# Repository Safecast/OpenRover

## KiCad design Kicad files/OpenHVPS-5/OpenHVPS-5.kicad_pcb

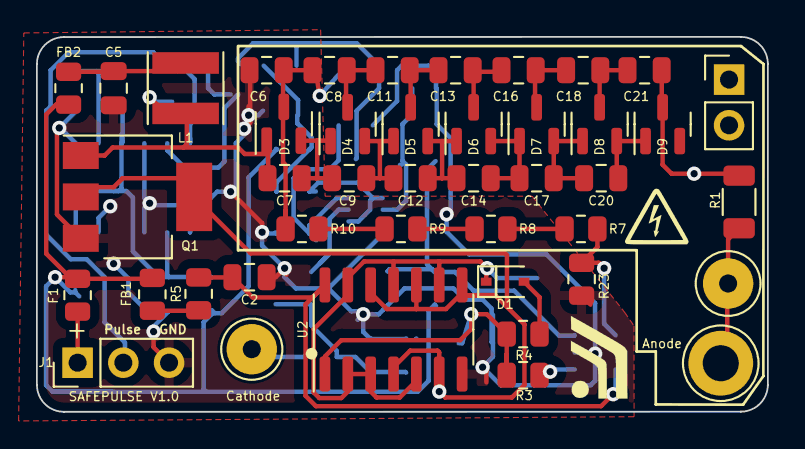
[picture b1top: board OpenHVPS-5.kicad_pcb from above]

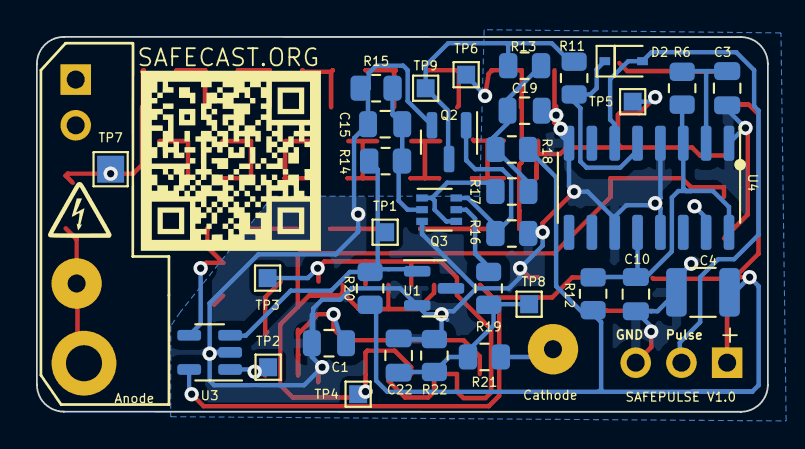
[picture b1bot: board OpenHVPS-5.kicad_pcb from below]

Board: 2 copper layers, 40.6 x 20.8 mm, 77 parts (35 on the bottom side), 43 nets.

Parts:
C1: 150pF; C_0805_2012Metric
C2, C5, C10: 1uF; C_0805_2012Metric
C3, C15: 1nF; C_0805_2012Metric
C4: 10uF; C_1210_3225Metric
C6, C7, C8, C9, C11, C12, C13, C14, C16, C17, C18, C19, C20, C21: 0.1uF; C_0805_2012Metric
C22: 360pF; C_0805_2012Metric
D1, D2: BAS16J; D_SOD-323
D3, D4, D5, D6, D7, D8, D9: BAV23; SOT-23
F1: Polyfuse; R_0805_2012Metric
FB1, FB2: BKP2125HS221-T; R_0805_2012Metric
H1: Cathode; TestPoint_Loop_D2.60mm_Drill1.4mm_Beaded
H2: Anode; TestPoint_Loop_D3.50mm_Drill1.4mm_Beaded
H2#2: Anode; TestPoint_Loop_D3.80mm_Drill2.0mm
J1: Conn_01x03_Male; PinHeader_1x03_P2.54mm_Vertical
L1: 2.2uH; L_Taiyo-Yuden_MD-4040
Q1: FQT7N10; SOT-223-3_TabPin2
Q2: BC846A; SOT-23
Q3: MMDT3906; SOT-363_SC-70-6
R1: 10M; R_1206_3216Metric
R3, R4: 100K; R_0805_2012Metric
R5, R12: 100; R_0805_2012Metric
R6: 121k; R_0805_2012Metric
R7, R8, R9, R10: 22M; R_0805_2012Metric
R11: 33k; R_0805_2012Metric
R13, R19: 100k; R_0805_2012Metric
R14: 1M5; R_0805_2012Metric
R15: 392k; R_0805_2012Metric
R16: 1M; R_0805_2012Metric
R17: 499k; R_0805_2012Metric
R18: 1k; R_0805_2012Metric
R20: 560K; R_0805_2012Metric
R21: 47k; R_0805_2012Metric
R22: 20k; R_0805_2012Metric
R23: 3.16M; R_0805_2012Metric
TP1, TP2, TP3, TP4, TP5, TP6, TP8, TP9: TestPoint; TestPoint_Pad_1.0x1.0mm
TP7: TestPoint; TestPoint_Pad_1.5x1.5mm
U1: MAX6008AEUR+T; SOT-23
U2: 74HC14; SOIC-14_3.9x8.7mm_P1.27mm
U3: MAX4162; SOT-23-5
U4: CD14538BM; SOIC-16_3.9x9.9mm_P1.27mm

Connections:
+2V5: R14.1, R20.2, TP1.1, U1.1 (IN), U3.3 (+)
+3V3: C4.1, F1.2, FB1.1, FB2.1, R12.1, R18.2, R20.1
GND: C1.2, C2.2, C3.2, C4.2, C5.2, C6.1, C10.2, C15.2, C19.2, C22.2, J1.3, Q1.3 (S), Q2.2 (E), Q3.3 (C2), R15.2, R16.2, R22.2, R23.2, U1.2 (OUT), U2.7 (GND), U3.2 (V-), U4.1 (VSS), U4.4 (Clk+), U4.8 (VSS), U4.11 (Clk-), U4.13 (R), U4.15 (VSS)
unnamed: C1.1, R3.1, R4.1, U2.1
unnamed: C2.1, R5.1, U2.14 (VCC), U3.5 (V+)
unnamed: C3.1, R6.2, U4.2 (RxCx)
unnamed: C5.1, FB2.2, L1.1
unnamed: C6.2, C8.1, D3.3 (K), R10.1, TP6.1
unnamed: C7.1, D3.1 (K), L1.2, Q1.1 (D), TP5.1
unnamed: C7.2, C9.1, D3.2 (A), D4.1 (K)
unnamed: C10.1, R6.1, R12.2, U4.3 (R), U4.12 (Clk+), U4.16 (VDD)
unnamed: C8.2, C11.1, D4.3 (K)
unnamed: C11.2, C13.1, D5.3 (K)
unnamed: C9.2, C12.1, D4.2 (A), D5.1 (K)
unnamed: C12.2, C14.1, D5.2 (A), D6.1 (K)
unnamed: C13.2, C16.1, D6.3 (K)
unnamed: C14.2, C17.1, D6.2 (A), D7.1 (K)
unnamed: C15.1, Q3.2 (B1), R14.2, R15.1
unnamed: C16.2, C18.1, D7.3 (K)
unnamed: C17.2, C20.1, D7.2 (A), D8.1 (K)
unnamed: C18.2, C21.1, D8.3 (K)
unnamed: C19.1, R13.1, R17.1, R18.1
unnamed: C20.2, D8.2 (A), D9.1 (K)
unnamed: C21.2, D9.3 (K), R1.1, TP7.1
unnamed: C22.1, R19.2, R21.2, R22.1, TP8.1
unnamed: D1.1 (K), TP3.1, U2.2, U2.3, U2.5, U2.9, U2.11, U2.13
unnamed: D1.2 (A), R4.2
unnamed: D2.1 (K), R11.1, U4.5 (Clk-)
unnamed: D2.2 (A), J1.2, U4.6 (Q)
unnamed: F1.1, J1.1
unnamed: FB1.2, R5.2
unnamed: H1.1, R21.1
unnamed: H2.1, H2#2.1, R1.2
unnamed: Q1.2 (G), TP4.1, U2.4, U2.6, U2.8, U2.10, U2.12
unnamed: Q2.1 (B), Q3.6 (C1), R16.1
unnamed: Q2.3 (C), R11.2, R13.2, TP9.1
unnamed: Q3.1 (E1), Q3.4 (E2), R17.2
unnamed: Q3.5 (B2), R19.1
unnamed: R3.2, TP2.1, U3.1
unnamed: R7.2, R8.1
unnamed: R8.2, R9.1
unnamed: R9.2, R10.2
unnamed: R7.1, R23.1, U3.4 (-)

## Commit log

2021-01-25 Moved TP7 to other side of board.
2021-01-25 Flipped TP7
2021-01-28 more clearly identify polarity on components
